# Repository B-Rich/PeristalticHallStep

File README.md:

PeristalticHallStep
===================

Peristaltic Pump Hall Sensor Board

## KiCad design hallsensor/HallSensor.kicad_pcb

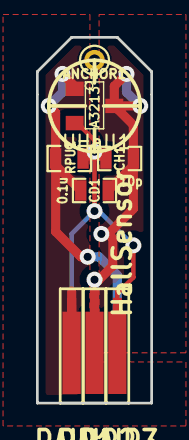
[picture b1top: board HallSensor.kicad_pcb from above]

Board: 2 copper layers, 6.3 x 20.3 mm, 8 parts (0 on the bottom side), 3 nets.

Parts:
ANCHOR1: CONN_1; PINTST
CD1: 0.1u; SM0603_Capa
CH1: 10p; SM0603_Capa
PAIR1, PAIR2, PAIR3: CONN_2; EDGE_2
RPU1: CONN_2; SM0603_Resistor
UHall1: A3213; SOT-23W

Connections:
/hall1: CH1.1, PAIR1.2, PAIR3.1, RPU1.2, UHall1.3
VCC: CD1.1, PAIR1.1, PAIR3.2, RPU1.1, UHall1.1
VSS: CD1.2, CH1.2, PAIR2.1, PAIR2.2, UHall1.2

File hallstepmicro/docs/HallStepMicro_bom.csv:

ref,value,datasheet,footprintCD1,0.1u,~,SM0805CD2,0.1u,~,SM0805CD3,0.1u,~,SM0805CD4,0.1u,~,SM0805CH1,10p,~,SM0805CH2,10p,~,SM0805CH3,10p,~,SM0805CH4,10p,~,SM0805DCM1,CONN_6,,SIL6-offset-0p005HALL6IN1,CONN_6,,SIL6-offset-0p005HALL6OUT1,CONN_6,,SIL6-offset-0p005IC1,ATTINY84A-SS,http://www.atmel.com/devices/ATTINY84A.aspx,SO14EISP6PIN1,CONN_3X2,,pin_array_3x2-offset-0p005RBRK1,5K,~,SM0805RDIR1,0,~,SM0805RENB1,5K,~,SM0805RESET1,CONN_2,,SIL-2RMODE1,5K,~,SM0805RPHASE1,5K,~,SM0805RPU1,CONN_2,,SM0805RPU2,CONN_2,http://www.allegromicro.com/en/Products/Magnetic-Digital-Pos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,SM0805RPU3,CONN_2,,SM0805RPU4,CONN_2,,SM0805RRESET1,5K,~,SM0805SENSE1,CONN_3,http://www.freescale.com/webapp/sps/site/prod_summary.jsp?co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,SIL3-offset-0p005STEPIN1,CONN_5X2,,PIN_ARRAY_5x2-offset-0p005UHall1,A3213,http://www.allegromicro.com/en/Products/Magnetic-Digital-Pos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,SOT-23WUHall2,A3213,http://www.allegromicro.com/en/Products/Magnetic-Digital-Pos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,SOT-23WUHall3,A3213,http://www.allegromicro.com/en/Products/Magnetic-Digital-Pos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,SOT-23WUHall4,A3213,http://www.allegromicro.com/en/Products/Magnetic-Digital-Pos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,SOT-23W

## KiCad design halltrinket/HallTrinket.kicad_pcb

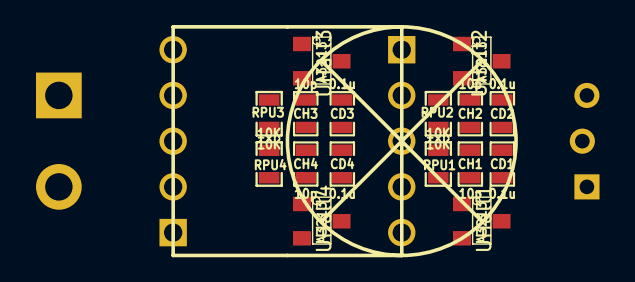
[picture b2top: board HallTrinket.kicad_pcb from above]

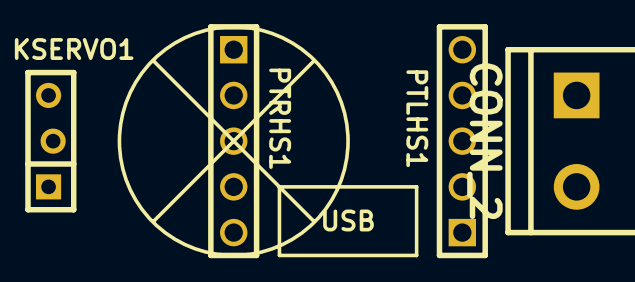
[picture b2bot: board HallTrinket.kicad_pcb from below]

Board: 2 copper layers, 20 parts (4 on the bottom side), 8 nets, no tracks yet.

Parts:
CD1, CD2, CD3, CD4: 0.1u; SM0603_Capa
CH1, CH2, CH3, CH4: 10p; SM0603_Capa
KSERVO1: CONN_3; SIL3-offset-0p005
PBAT1: CONN_2; bornier2
PTLHS1: CONN_5; PIN_ARRAY_5x1
PTRHS1: CONN_5; PIN_ARRAY_5x1
RPU1, RPU2, RPU3, RPU4: 10K; SM0603_Resistor
UHall1, UHall2, UHall3, UHall4: A3213; SOT-23W

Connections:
+BATT: PBAT1.2, PTLHS1.1
/PB0: KSERVO1.1, PTRHS1.4
/hallsensor1/hall1: CH1.1, PTRHS1.3, RPU1.2, UHall1.3
/hallsensor2/hall2: CH2.1, PTRHS1.2, RPU2.2, UHall2.3
/hallsensor3/hall3: CH3.1, PTLHS1.4, RPU3.2, UHall3.3
/hallsensor4/hall4: CH4.1, PTLHS1.3, RPU4.2, UHall4.3
VCC: CD1.1, CD2.1, CD3.1, CD4.1, KSERVO1.2, PTRHS1.1, RPU1.1, RPU2.1, RPU3.1, RPU4.1, UHall1.1, UHall2.1, UHall3.1, UHall4.1
VSS: CD1.2, CD2.2, CD3.2, CD4.2, CH1.2, CH2.2, CH3.2, CH4.2, KSERVO1.3, PBAT1.1, PTLHS1.2, UHall1.2, UHall2.2, UHall3.2, UHall4.2

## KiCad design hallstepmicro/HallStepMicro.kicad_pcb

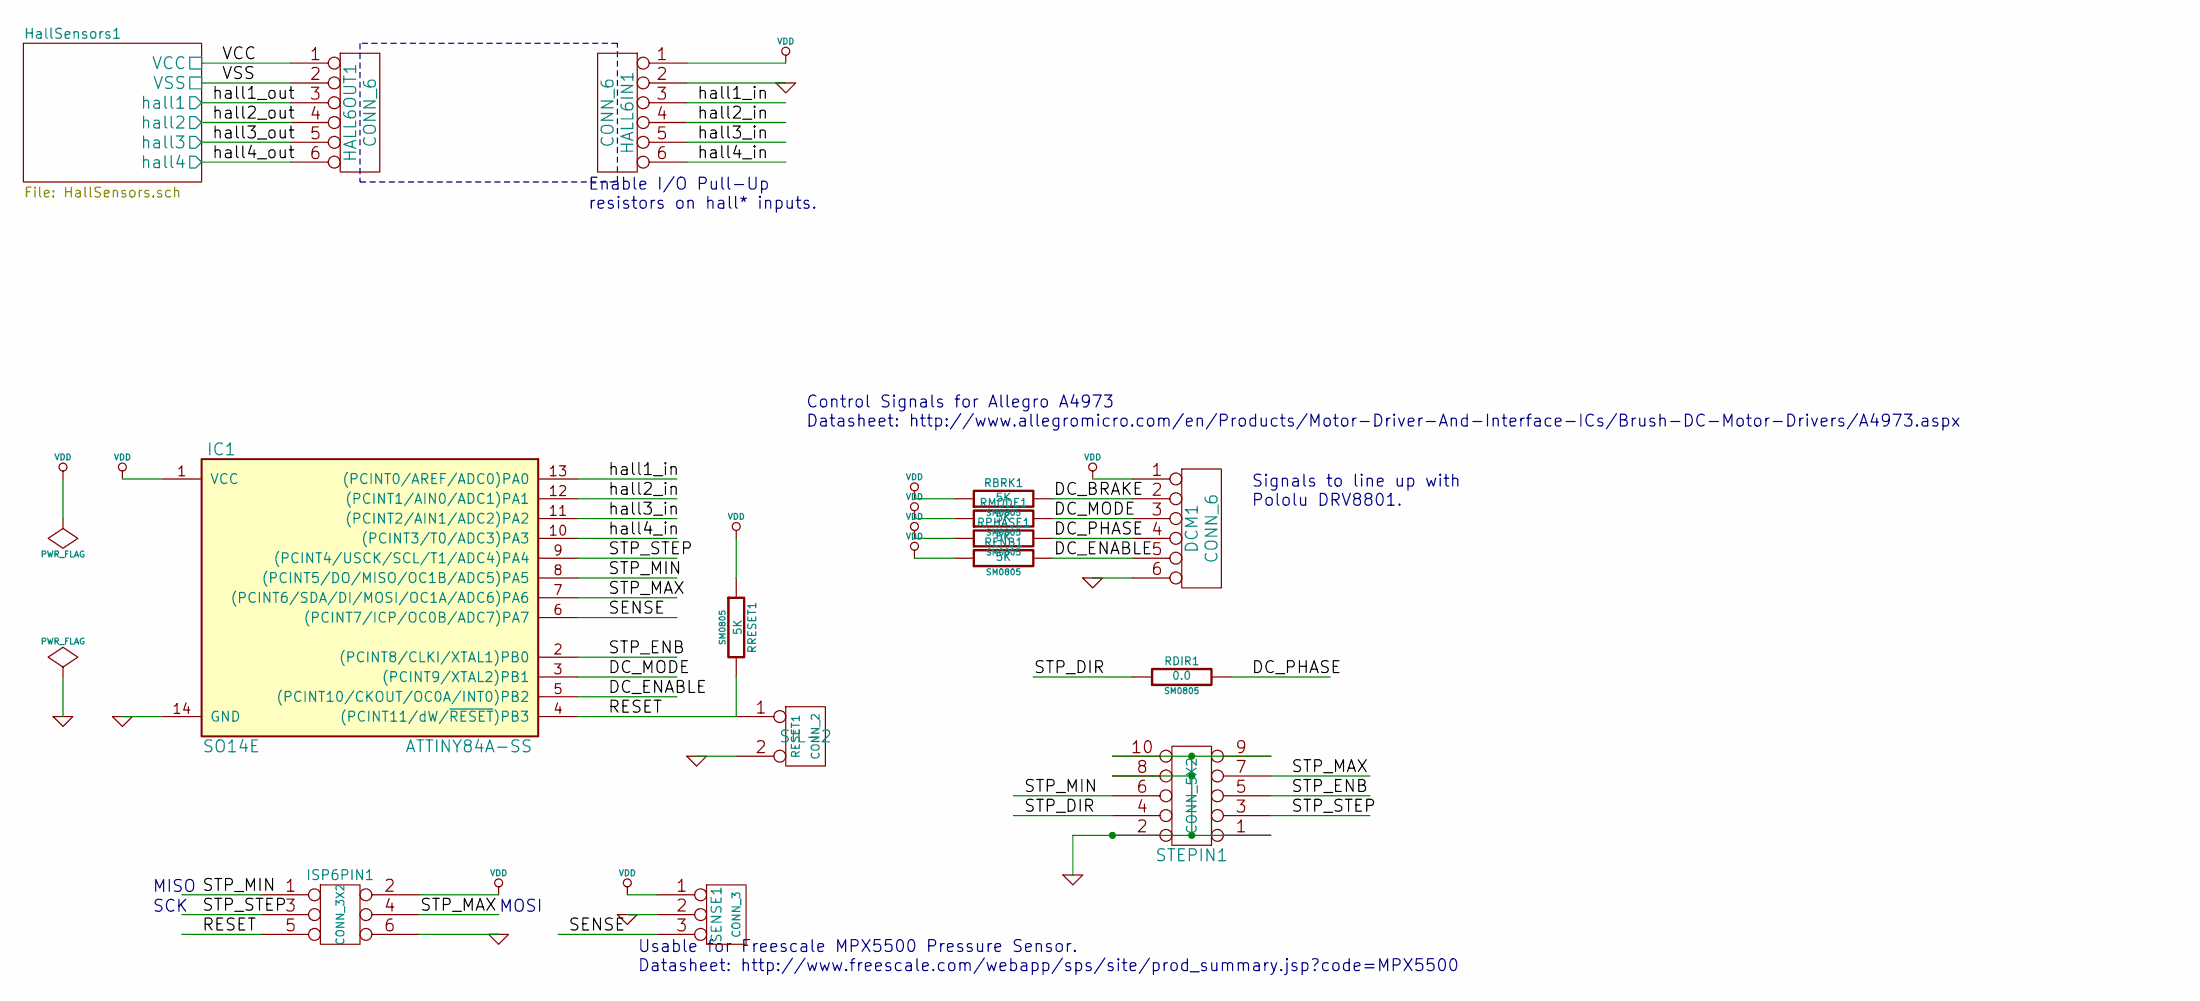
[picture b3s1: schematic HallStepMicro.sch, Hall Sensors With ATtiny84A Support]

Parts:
DCM1: CONN_6; SIL6-offset-0p005
HALL6IN1, HALL6OUT1: CONN_6; SIL6-offset-0p005
IC1: ATTINY84A-SS; SO14E
ISP6PIN1: CONN_3X2; pin_array_3x2-offset-0p005
RBRK1: 5K; SM0805
RDIR1: 0.0; SM0805
RENB1: 5K; SM0805
RESET1: CONN_2; SIL-2
RMODE1: 5K; SM0805
RPHASE1: 5K; SM0805
RRESET1: 5K; SM0805
SENSE1: CONN_3; SIL3-offset-0p005
STEPIN1: CONN_5X2; PIN_ARRAY_5x2-offset-0p005

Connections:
/DC_BRAKE: DCM1.2, RBRK1.2
/DC_ENABLE: DCM1.5, IC1.5 ((PCINT10/CKOUT/OC0A/INT0)PB2), RENB1.2
/DC_MODE: DCM1.3, IC1.3 ((PCINT9/XTAL2)PB1), RMODE1.2
/DC_PHASE: DCM1.4, RDIR1.2, RPHASE1.2
/HallSensors1/hall1: HALL6OUT1.3; also elsewhere on the board
/HallSensors1/hall2: HALL6OUT1.4; also elsewhere on the board
/HallSensors1/hall3: HALL6OUT1.5; also elsewhere on the board
/HallSensors1/hall4: HALL6OUT1.6; also elsewhere on the board
/RESET: IC1.4 ((PCINT11/dW/~RESET~)PB3), ISP6PIN1.5, RESET1.1, RRESET1.2
/SENSE: IC1.6 ((PCINT7/ICP/OC0B/ADC7)PA7), SENSE1.3
/STP_DIR: RDIR1.1, STEPIN1.4
/STP_ENB: IC1.2 ((PCINT8/CLKI/XTAL1)PB0), STEPIN1.5
/STP_MAX: IC1.7 ((PCINT6/SDA/DI/MOSI/OC1A/ADC6)PA6), ISP6PIN1.4, STEPIN1.7
/STP_MIN: IC1.8 ((PCINT5/DO/MISO/OC1B/ADC5)PA5), ISP6PIN1.1, STEPIN1.6
/STP_STEP: IC1.9 ((PCINT4/USCK/SCL/T1/ADC4)PA4), ISP6PIN1.3, STEPIN1.3
/hall1_in: HALL6IN1.3, IC1.13 ((PCINT0/AREF/ADC0)PA0)
/hall2_in: HALL6IN1.4, IC1.12 ((PCINT1/AIN0/ADC1)PA1)
/hall3_in: HALL6IN1.5, IC1.11 ((PCINT2/AIN1/ADC2)PA2)
/hall4_in: HALL6IN1.6, IC1.10 ((PCINT3/T0/ADC3)PA3)
GND: DCM1.6, HALL6IN1.2, IC1.14 (GND), ISP6PIN1.6, RESET1.2 (PM), SENSE1.2 (PM), STEPIN1.1, STEPIN1.2, STEPIN1.8, STEPIN1.9, STEPIN1.10
VCC: HALL6OUT1.1; also elsewhere on the board
VDD: DCM1.1, HALL6IN1.1, IC1.1 (VCC), ISP6PIN1.2, RBRK1.1, RENB1.1, RMODE1.1, RPHASE1.1, RRESET1.1, SENSE1.1
VSS: HALL6OUT1.2; also elsewhere on the board

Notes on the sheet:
Enable I/O Pull-Up resistors on hall* inputs.
Control Signals for Allegro A4973 Datasheet: http://www.allegromicro.com/en/Products/Motor-Driver-And-Interface-ICs/Brush-DC-Motor-Drivers/A4973.aspx
Signals to line up with Pololu DRV8801.
MISO
SCK
MOSI
Usable for Freescale MPX5500 Pressure Sensor. Datasheet: http://www.freescale.com/webapp/sps/site/prod_summary.jsp?code=MPX5500

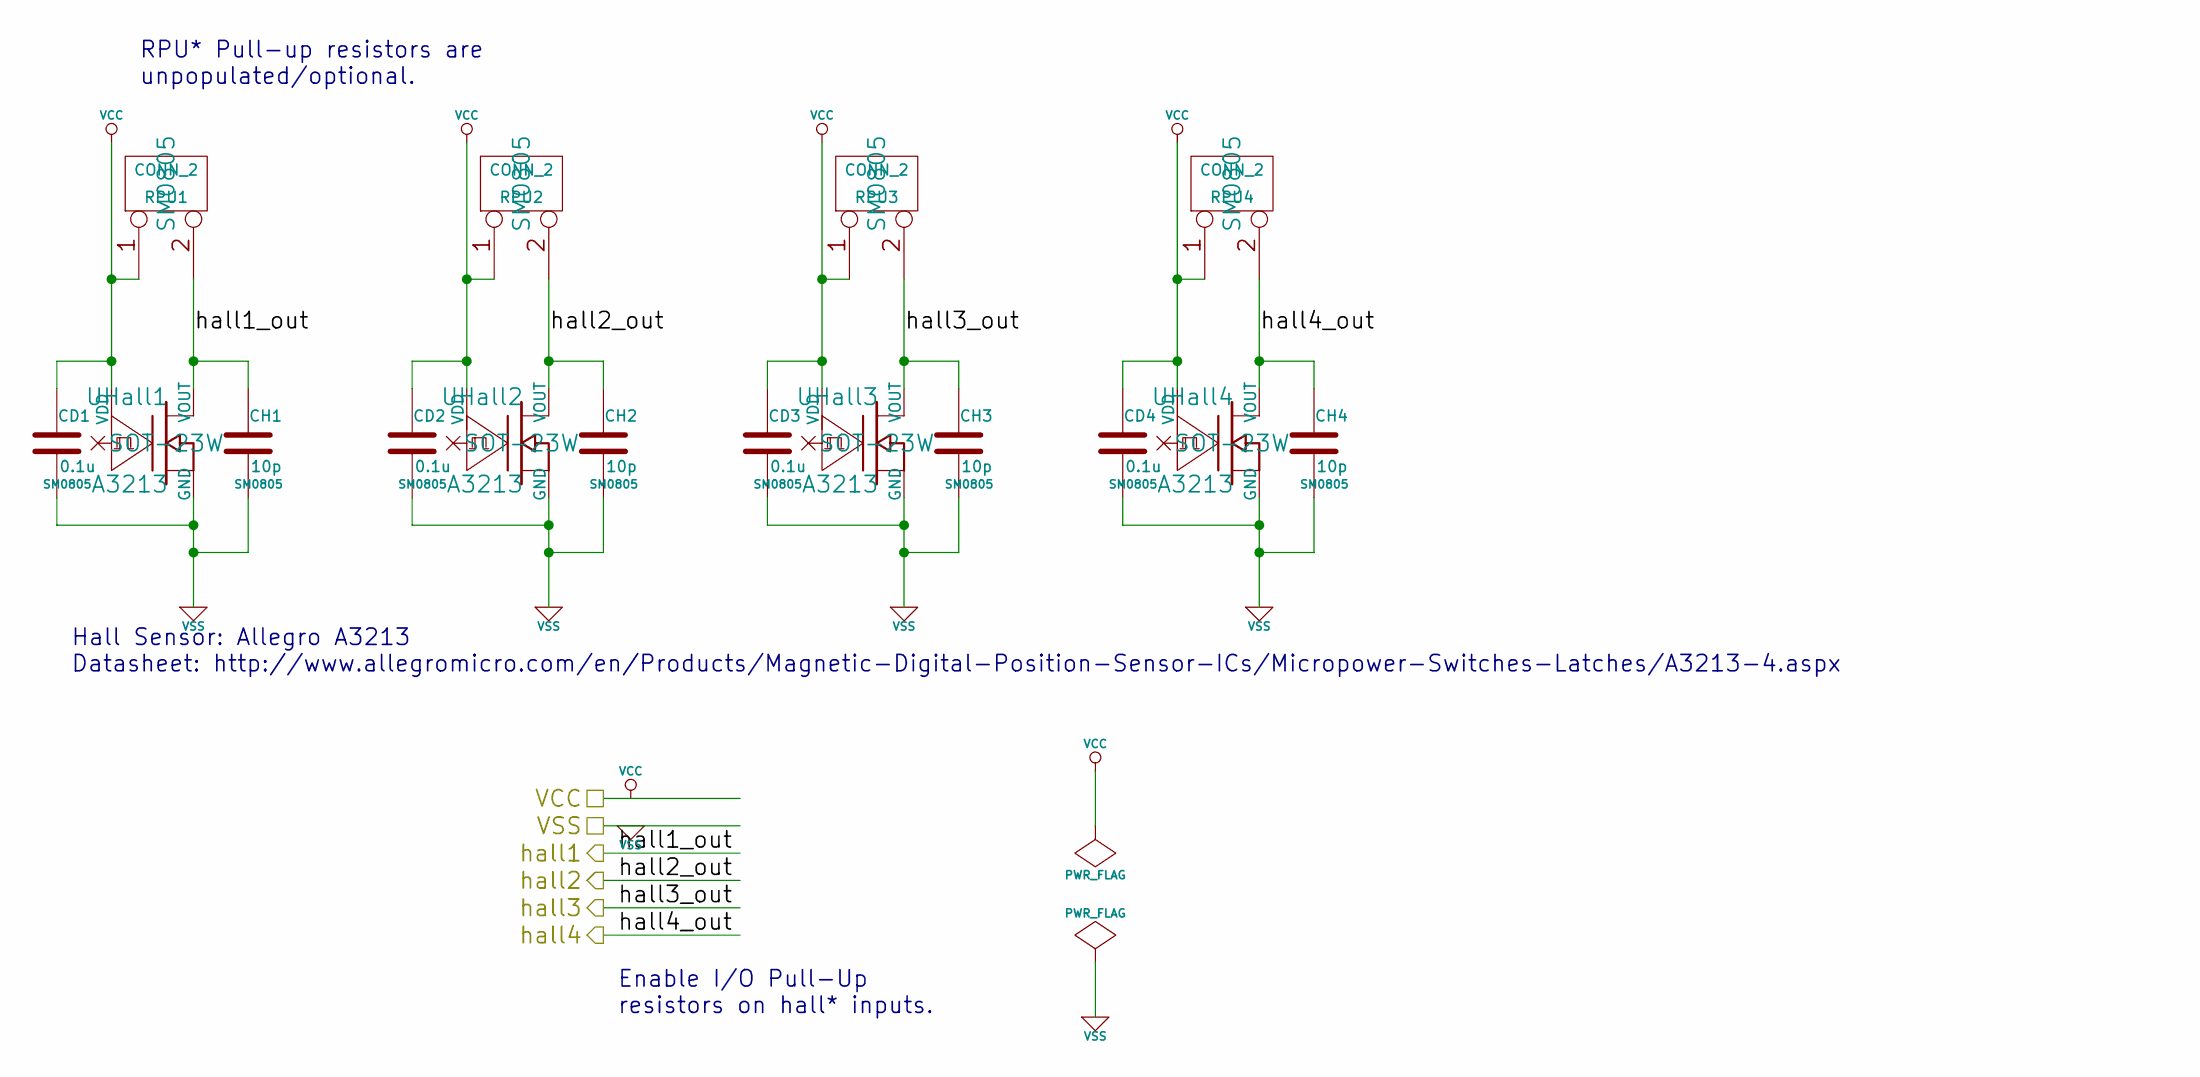
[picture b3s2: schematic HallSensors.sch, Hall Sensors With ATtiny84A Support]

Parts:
CD1, CD2, CD3, CD4: 0.1u; SM0805
CH1, CH2, CH3, CH4: 10p; SM0805
RPU1, RPU2, RPU3, RPU4: CONN_2; SM0805
UHall1, UHall2, UHall3, UHall4: A3213; SOT-23W

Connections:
/HallSensors1/hall1: CH1.1, RPU1.2 (PM), UHall1.3 (VOUT); also elsewhere on the board
/HallSensors1/hall2: CH2.1, RPU2.2 (PM), UHall2.3 (VOUT); also elsewhere on the board
/HallSensors1/hall3: CH3.1, RPU3.2 (PM), UHall3.3 (VOUT); also elsewhere on the board
/HallSensors1/hall4: CH4.1, RPU4.2 (PM), UHall4.3 (VOUT); also elsewhere on the board
VCC: CD1.1, CD2.1, CD3.1, CD4.1, RPU1.1, RPU2.1, RPU3.1, RPU4.1, UHall1.1 (VDD), UHall2.1 (VDD), UHall3.1 (VDD), UHall4.1 (VDD); also elsewhere on the board
VSS: CD1.2, CD2.2, CD3.2, CD4.2, CH1.2, CH2.2, CH3.2, CH4.2, UHall1.2 (GND), UHall2.2 (GND), UHall3.2 (GND), UHall4.2 (GND); also elsewhere on the board

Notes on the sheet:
Enable I/O Pull-Up resistors on hall* inputs.
RPU* Pull-up resistors are unpopulated/optional.
Hall Sensor: Allegro A3213 Datasheet: http://www.allegromicro.com/en/Products/Magnetic-Digital-Position-Sensor-ICs/Micropower-Switches-Latches/A3213-4.aspx

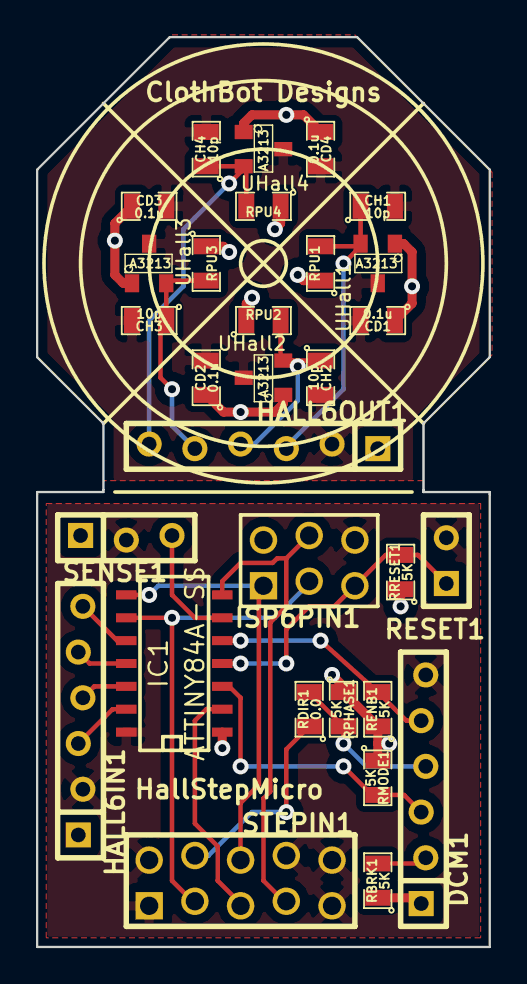
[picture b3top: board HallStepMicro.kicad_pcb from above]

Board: 2 copper layers, 25.1 x 50.5 mm, 30 parts (0 on the bottom side), 23 nets.

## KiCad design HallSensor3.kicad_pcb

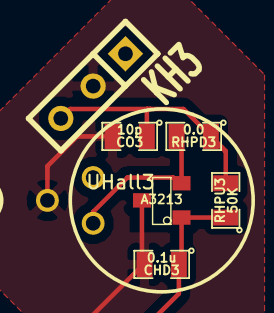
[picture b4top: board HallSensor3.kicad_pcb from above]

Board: 2 copper layers, 7 parts (1 on the bottom side), 4 nets.

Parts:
CHD3: 0.1u; SM0805
CO3: 10p; SM0805
K3: CONN_3; TO92H
KH3: CONN_3; SIL-3
RHPD3: 0.0; SM0805
RHPU3: 50K; SM0805
UHall3: A3213; SOT23-SPECIAL

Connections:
+5V: CHD3.1, K3.1, KH3.1, RHPU3.1, UHall3.1
/HALL: K3.3, RHPD3.2, UHall3.3
/VOUT: CO3.1, KH3.3, RHPD3.1, RHPU3.2
GND: CHD3.2, CO3.2, K3.2, KH3.2, UHall3.2

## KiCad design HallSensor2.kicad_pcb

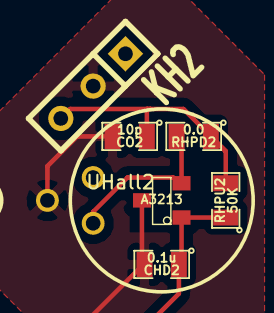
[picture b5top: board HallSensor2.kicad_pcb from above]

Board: 2 copper layers, 7 parts (1 on the bottom side), 4 nets.

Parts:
CHD2: 0.1u; SM0805
CO2: 10p; SM0805
K2: CONN_3; TO92H
KH2: CONN_3; SIL-3
RHPD2: 0.0; SM0805
RHPU2: 50K; SM0805
UHall2: A3213; SOT23-SPECIAL

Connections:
+5V: CHD2.1, K2.1, KH2.1, RHPU2.1, UHall2.1
/HALL: K2.3, RHPD2.2, UHall2.3
/VOUT: CO2.1, KH2.3, RHPD2.1, RHPU2.2
GND: CHD2.2, CO2.2, K2.2, KH2.2, UHall2.2

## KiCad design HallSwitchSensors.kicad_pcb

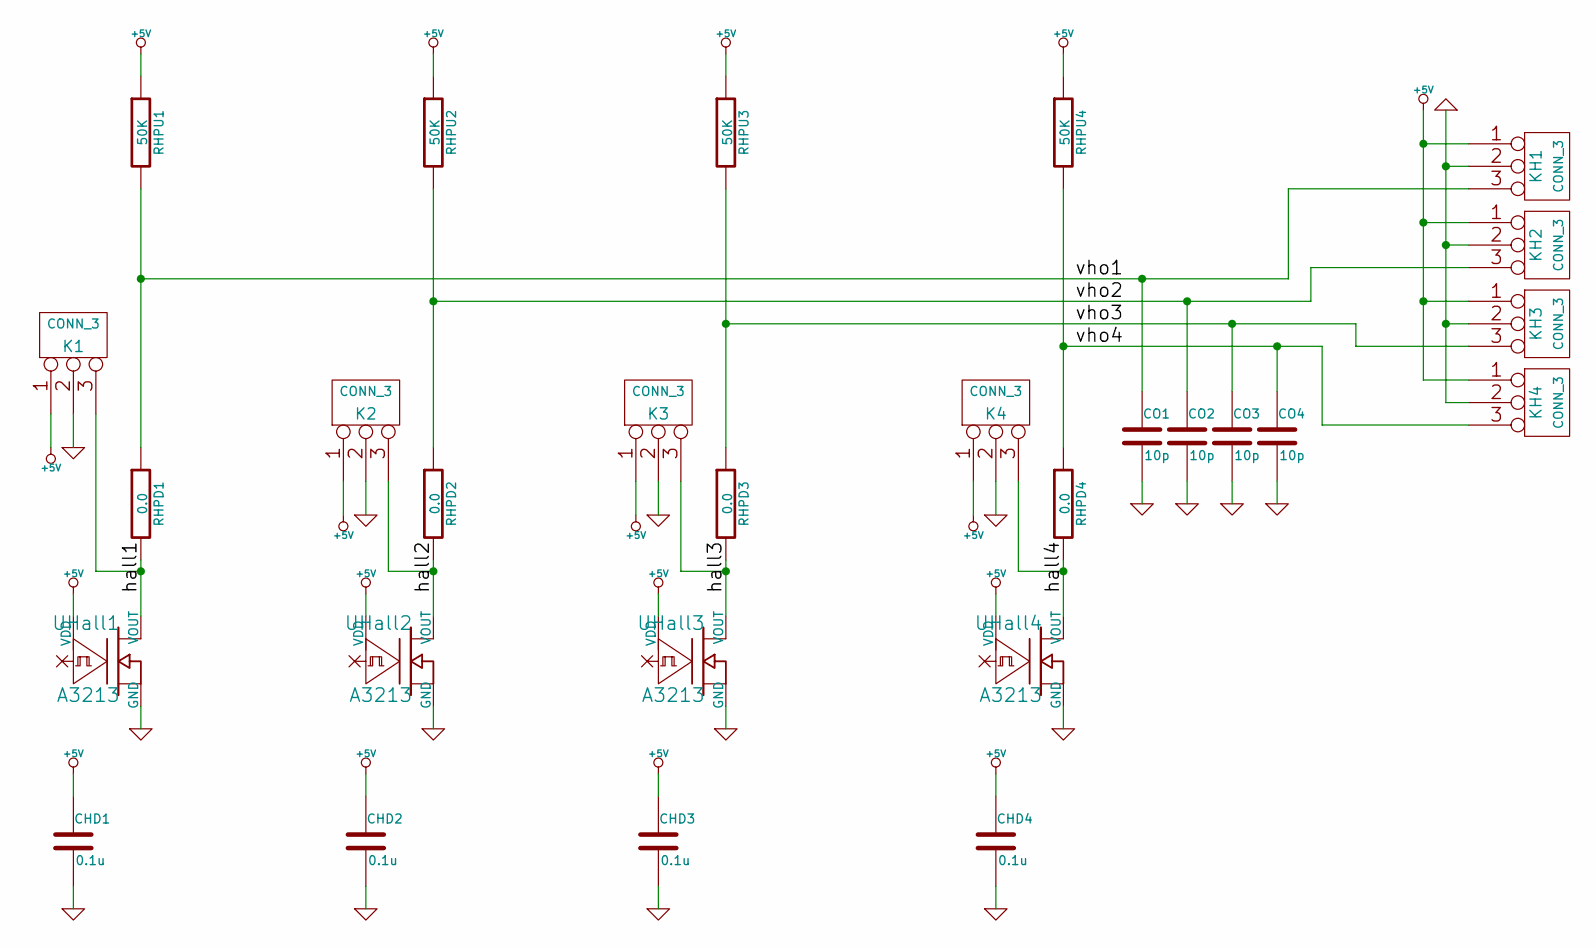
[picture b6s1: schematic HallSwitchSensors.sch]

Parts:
CHD1, CHD2, CHD3, CHD4: 0.1u
CO1, CO2, CO3, CO4: 10p
K1, K2, K3, K4: CONN_3
KH1, KH2, KH3, KH4: CONN_3
RHPD1, RHPD2, RHPD3, RHPD4: 0.0
RHPU1, RHPU2, RHPU3, RHPU4: 50K
UHall1, UHall2, UHall3, UHall4: A3213

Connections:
+5V: CHD1.1, CHD2.1, CHD3.1, CHD4.1, K1.1, K2.1, K3.1, K4.1, KH1.1, KH2.1, KH3.1, KH4.1, RHPU1.1, RHPU2.1, RHPU3.1, RHPU4.1, UHall1.1 (VDD), UHall2.1 (VDD), UHall3.1 (VDD), UHall4.1 (VDD)
/hall1: K1.3, RHPD1.2, UHall1.3 (VOUT)
/hall2: K2.3, RHPD2.2, UHall2.3 (VOUT)
/hall3: K3.3, RHPD3.2, UHall3.3 (VOUT)
/hall4: K4.3, RHPD4.2, UHall4.3 (VOUT)
/vho1: CO1.1, KH1.3, RHPD1.1, RHPU1.2
/vho2: CO2.1, KH2.3, RHPD2.1, RHPU2.2
/vho3: CO3.1, KH3.3, RHPD3.1, RHPU3.2
/vho4: CO4.1, KH4.3, RHPD4.1, RHPU4.2
GND: CHD1.2, CHD2.2, CHD3.2, CHD4.2, CO1.2, CO2.2, CO3.2, CO4.2, K1.2 (PM), K2.2 (PM), K3.2 (PM), K4.2 (PM), KH1.2 (PM), KH2.2 (PM), KH3.2 (PM), KH4.2 (PM), UHall1.2 (GND), UHall2.2 (GND), UHall3.2 (GND), UHall4.2 (GND)

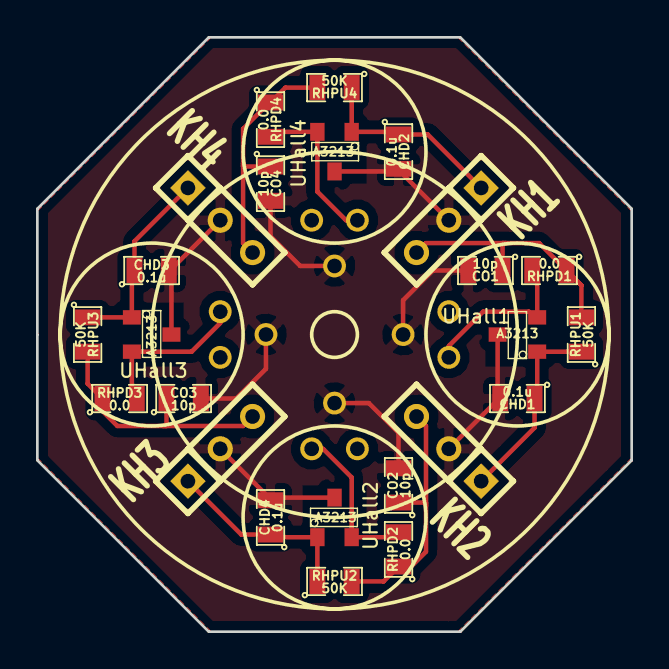
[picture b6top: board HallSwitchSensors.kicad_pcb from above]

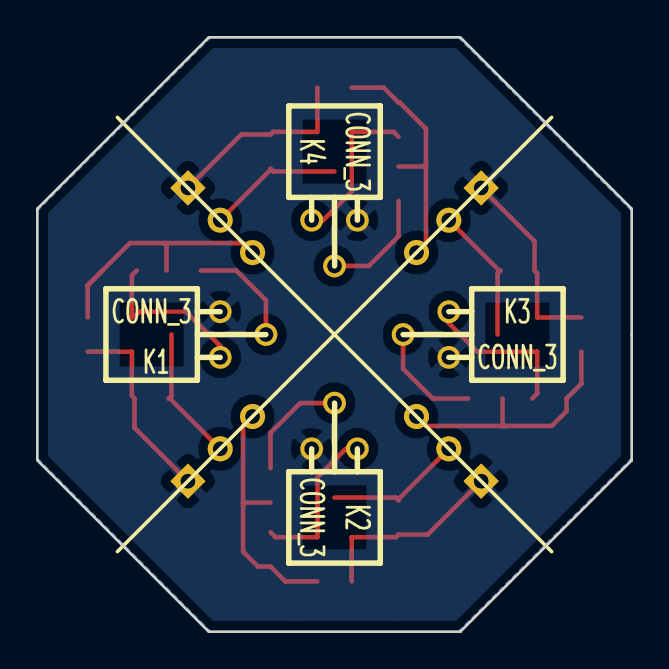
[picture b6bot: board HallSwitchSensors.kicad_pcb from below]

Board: 2 copper layers, 33.0 x 33.0 mm, 28 parts (4 on the bottom side), 10 nets.

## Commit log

2013-09-27 Initial commit in public repository.
2013-09-27 Added exported formats to test Upverter.
2013-09-27 Fixed up fill using Windows version of KiCAD
    Fewer crashing in Windows version of KiCAD getting copper fill to
    behave. Now to try again on MacOSX based on what I know here.
2013-09-28 Reworking as multi-schematic hierarchy. Doesn't look like kicad is truly hierarchical in the one-master to many-instances sense, but still investigating.
2013-09-28 Moving files into subdirectory.
2013-09-29 Initial add of stepper-signaled, hall-sensor micro controller board pair.
2013-09-30 More rework.
2013-09-30 Added layouts.mod.
2013-09-30 Added keepouts, fill and grew TO-92HL
    Created TO-92HL (long) for mask showing larger placement area.
2013-09-30 Working on layout.
2013-09-30 Simplify. Simplify. Simplify.
2013-09-30 Cleaned up keepouts.
2013-10-01 More workin' the layout.
2013-10-01 Modified 3+ pin headers to offset pins +/-0.005"
    Using SparkFun trick to offset pin holes to make headers more secure.
2013-10-01 Cleaned up routing on sensor mount.
2013-10-01 Adding OSHPark Minimum rule settings.
2013-10-01 Shrinking sensor mount
    Shrinking sensor mount dimensions. Intermediate checkin before
    repositioning connector.
2013-10-01 Cleaned up routing.
2013-10-01 Misc clean-up. Considered adding back TO92 case option but made design too cluttered.
2013-10-01 Added comment about using Freescale MPX5500 pressure sensor.
2013-10-02 Refined wiring in micro zone.
2013-10-02 Tweaking layout routing.
2013-10-03 Added optional pullup resistors to sensor board.
2013-10-03 Minor tweaks
    - Moving grid origin to bottom-left corner of layouts.
    - Tweaked RESET1 test size; text resizing causes Mac KiCad to crash.
    - moved dimensions off silkscreen layer.
2013-10-03 The "grid_origin" parameter causes kiad 2013-mar-25-stable on Mac to crash. Manually deleting it for now.
2013-10-03 Running DRC to generate filled zones causes churn in underlying file. Space+CR/LF are only differences.
2013-10-04 Syncing up backup file
2013-10-04 Moving two boards against each other.
2013-10-04 Repositioned boards for right-angle cuts and cleaned up silkscreen layers.
2013-10-04 Resizing edges to come under 2"x1"
2013-10-04 Added extra clearance to copper pour
    Dimension problem was probably too-large silk screen, but explicitly
    satisfying DRC is a good thing anyway.
2013-10-04 Merged two boards into one for first batch. Will split it into separate boards in next rev.
2013-10-04 Adding some documentation & related markup.
2013-10-07 Initial add of single-sensor board.
2013-10-07 Revised copper pour and and routing.
2013-10-07 Added alignment vias at +/-0.1"
2013-10-07 Fixed via in micro pad.
2013-10-09 Pulling in OpenSCAD model of sensor coupler for peristaltic pump carried by Adafruit. Added WIP for Adafruit trinket-compatible sensor board.
2013-10-09 Added OHW Logo.
2013-10-10 Misc rework.
2013-10-10 Adjusted EDGE_2 silk layer.
2013-10-10 Tweaked copper pour & via placement.
